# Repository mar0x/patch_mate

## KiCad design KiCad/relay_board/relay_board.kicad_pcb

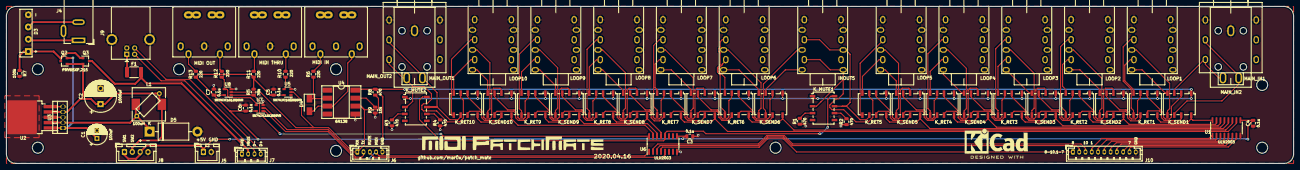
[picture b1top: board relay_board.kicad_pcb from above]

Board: 2 copper layers, 410.0 x 50.0 mm, 83 parts (0 on the bottom side), 136 nets.

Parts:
C1: 100uF; CP_Radial_D6.3mm_P2.50mm
C2: 1000uF; CP_Radial_D10.0mm_P5.00mm
C3, C4, C5, C6, C7: 0.1u; C_0805_2012Metric
D3: RS202-BP; Diode_Bridge_KBP20x
D4: D; D_SMA
D5: 1N5822; D_DO-201AD_P15.24mm_Horizontal
F1: MF-MSMF050-2; Fuse_1812_4532Metric_Pad1.30x3.40mm_HandSolder
INOUT5: AudioJack3_Dual_Switch; CK635-037
J1, J2, J3: DIN5MIDI-OOTDTY
J4: DS-210; BarrelJack_Wuerth_6941xx301002
J5: JST B2B-XH-A; JST_XH_B2B-XH-A_1x02_P2.50mm_Vertical
J6: JST B5B-PH-K-S; JST_PH_B5B-PH-K_1x05_P2.00mm_Vertical
J7: JST B4B-PH-K-S; JST_PH_B4B-PH-K_1x04_P2.00mm_Vertical
J8: JST B4B-XH-A; JST_XH_B4B-XH-A_1x04_P2.50mm_Vertical
J9: DS1099; USB_B_OST_USB-B1HSxx_Horizontal
J10: JST B11B-PH-K-S; JST_PH_B11B-PH-K_1x11_P2.00mm_Vertical
K_MUTE1, K_MUTE2: G6K-2; Relay_DPDT_Omron_G6K-2F-Y
K_RET1, K_RET2, K_RET3, K_RET4, K_RET5, K_RET6, K_RET7, K_RET8, K_RET9, K_RET10: G6K-2; Relay_DPDT_Omron_G6K-2F-Y
K_SEND1, K_SEND2, K_SEND3, K_SEND4, K_SEND5, K_SEND6, K_SEND7, K_SEND8, K_SEND9, K_SEND10: G6K-2; Relay_DPDT_Omron_G6K-2F-Y
L1: 100uH; L_10.4x10.4_H4.8
L2: 100uH; L_Axial_L7.0mm_D3.3mm_P10.16mm_Horizontal_Fastron_MICC
LOOP1, LOOP2, LOOP3, LOOP4, LOOP5, LOOP6, LOOP7, LOOP8, LOOP9, LOOP10: AudioJack3_Dual_Switch; CK635-037
MAIN_IN1: CK635-041A
MAIN_IN2: HLJ0544*; phone-jack-6.3
MAIN_OUT1: CK635-041A
MAIN_OUT2: HLJ0544*; phone-jack-6.3
Q2, Q3: PMV65XP,215; SOT-23
R1, R2, R3, R4, R8: 470; R_0805_2012Metric
R5: 39k; R_0805_2012Metric
R6, R10, R11, R12, R13: 220; R_0805_2012Metric
R7: 100k; R_0805_2012Metric
R9: 10k; R_0805_2012Metric
U1, U6: ULN2003; SOIC-16_3.9x9.9mm_P1.27mm
U2: LM2576S-5.0; TO-263-5_TabPin3
U3: LM2576HVT-5.0; TO-220-5_Vertical
U4: 6N138; DIP-8_W8.89mm_SMDSocket_LongPads
U5, U7, U8: SN74LVC1G125DBVR; SOT-23-5

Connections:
+5V: C3.2, C4.2, C5.2, C6.2, C7.2, J5.1, J8.1, J8.3, K_MUTE1.1, K_MUTE2.1, K_RET1.1, K_RET2.1, K_RET3.1, K_RET4.1, K_RET5.1, K_RET6.1, K_RET7.1, K_RET8.1, K_RET9.1, K_RET10.1, K_SEND1.1, K_SEND2.1, K_SEND3.1, K_SEND4.1, K_SEND5.1, K_SEND6.1, K_SEND7.1, K_SEND8.1, K_SEND9.1, K_SEND10.1, R5.2, R8.2, R11.1, R13.1, U1.9, U4.8, U5.5, U6.9, U7.5, U8.5
+9V: D3.1, Q2.3, Q3.1, R7.1
D+: J7.4, J9.3
D-: J7.3, J9.2
GND: C1.2, C2.2, C3.1, C4.1, C5.1, C6.1, C7.1, D3.4, D5.2, INOUT5.S1, INOUT5.S2, INOUT5.SN1, INOUT5.SN2, J2.2, J3.2, J5.2, J6.5, J7.1, J8.4, J9.4, J9.5, J10.11, LOOP1.S1, LOOP1.S2, LOOP1.SN1, LOOP1.SN2, LOOP2.S1, LOOP2.S2, LOOP2.SN1, LOOP2.SN2, LOOP3.S1, LOOP3.S2, LOOP3.SN1, LOOP3.SN2, LOOP4.S1, LOOP4.S2, LOOP4.SN1, LOOP4.SN2, LOOP5.S1, LOOP5.S2, LOOP5.SN1, LOOP5.SN2, LOOP6.S1, LOOP6.S2, LOOP6.SN1, LOOP6.SN2, LOOP7.S1, LOOP7.S2, LOOP7.SN1, LOOP7.SN2, LOOP8.S1, LOOP8.S2, LOOP8.SN1, LOOP8.SN2, LOOP9.S1, LOOP9.S2, LOOP9.SN1, LOOP9.SN2, LOOP10.S1, LOOP10.S2, LOOP10.SN1, LOOP10.SN2, MAIN_IN1.S, MAIN_IN1.SN, MAIN_IN2.S, MAIN_OUT1.S, MAIN_OUT1.SN, MAIN_OUT2.S, R1.1, R2.1, R3.1, R4.1, R7.2, R9.1, U1.8, U2.3, U2.5, U3.3, U3.5, U4.5, U5.1, U5.3, U6.8, U7.3, U8.3
LOOP1: J10.4, U1.1
LOOP1_R: K_SEND1.6, MAIN_IN1.R, MAIN_IN2.R
LOOP1_T: K_SEND1.3, MAIN_IN1.T, MAIN_IN2.T
LOOP2: J10.5, U1.2
LOOP3: J10.6, U1.3
LOOP4: J10.7, U1.4
LOOP5: J10.8, U1.5
LOOP5_R: INOUT5.R1, INOUT5.RN2, K_MUTE1.7, K_RET5.6
LOOP5_T: INOUT5.T1, INOUT5.TN2, K_MUTE1.2, K_RET5.3
LOOP6: J10.9, U1.6
LOOP6_R: INOUT5.R2, K_SEND6.6
LOOP6_T: INOUT5.T2, K_SEND6.3
LOOP7: J10.10, U1.7
LOOP8: J10.1, U6.4
LOOP9: J10.2, U6.3
LOOP10: J10.3, U6.2
LOOP10_R: K_MUTE2.7, K_RET10.6, MAIN_OUT1.R, MAIN_OUT2.R
LOOP10_T: K_MUTE2.2, K_RET10.3, MAIN_OUT1.T, MAIN_OUT2.T
MIDI_MODE: J6.4, U6.1, U7.1
MIDI_OUT: R12.2, U7.4, U8.4
MUTE: J6.3, U6.5
unnamed: D3.2, J4.1
unnamed: D3.3, J4.2
unnamed: D4.1, R6.1, U4.2
unnamed: D4.2, J1.5, U4.3
unnamed: F1.1, J9.1
unnamed: J1.4, R6.2
unnamed: J2.4, R11.2
unnamed: J2.5, R10.1
unnamed: J3.4, R13.2
unnamed: J3.5, R12.1
unnamed: K_MUTE1.3, R1.2
unnamed: K_MUTE1.6, R2.2
unnamed: K_MUTE2.3, R3.2
unnamed: K_MUTE2.6, R4.2
unnamed: K_RET1.2, K_SEND1.2
unnamed: K_RET1.3, K_SEND2.3
unnamed: K_RET1.4, LOOP1.T1
unnamed: K_RET1.5, LOOP1.R1
unnamed: K_RET1.6, K_SEND2.6
unnamed: K_RET1.7, K_SEND1.7
unnamed: K_RET2.2, K_SEND2.2
unnamed: K_RET2.3, K_SEND3.3
unnamed: K_RET2.4, LOOP2.T1
unnamed: K_RET2.5, LOOP2.R1
unnamed: K_RET2.6, K_SEND3.6
unnamed: K_RET2.7, K_SEND2.7
unnamed: K_RET3.2, K_SEND3.2
unnamed: K_RET3.3, K_SEND4.3
unnamed: K_RET3.4, LOOP3.T1
unnamed: K_RET3.5, LOOP3.R1
unnamed: K_RET3.6, K_SEND4.6
unnamed: K_RET3.7, K_SEND3.7
unnamed: K_RET4.2, K_SEND4.2
unnamed: K_RET4.3, K_SEND5.3
unnamed: K_RET4.4, LOOP4.T1
unnamed: K_RET4.5, LOOP4.R1
unnamed: K_RET4.6, K_SEND5.6
unnamed: K_RET4.7, K_SEND4.7
unnamed: K_RET5.2, K_SEND5.2
unnamed: K_RET5.4, LOOP5.T1
unnamed: K_RET5.5, LOOP5.R1
unnamed: K_RET5.7, K_SEND5.7
unnamed: K_RET6.2, K_SEND6.2
unnamed: K_RET6.3, K_SEND7.3
unnamed: K_RET6.4, LOOP6.T1
unnamed: K_RET6.5, LOOP6.R1
unnamed: K_RET6.6, K_SEND7.6
unnamed: K_RET6.7, K_SEND6.7
unnamed: K_RET7.2, K_SEND7.2
unnamed: K_RET7.3, K_SEND8.3
unnamed: K_RET7.4, LOOP7.T1
unnamed: K_RET7.5, LOOP7.R1
unnamed: K_RET7.6, K_SEND8.6
unnamed: K_RET7.7, K_SEND7.7
unnamed: K_RET8.2, K_SEND8.2
unnamed: K_RET8.3, K_SEND9.3
unnamed: K_RET8.4, LOOP8.T1
unnamed: K_RET8.5, LOOP8.R1
unnamed: K_RET8.6, K_SEND9.6
unnamed: K_RET8.7, K_SEND8.7
unnamed: K_RET9.2, K_SEND9.2
unnamed: K_RET9.3, K_SEND10.3
unnamed: K_RET9.4, LOOP9.T1
unnamed: K_RET9.5, LOOP9.R1
unnamed: K_RET9.6, K_SEND10.6
unnamed: K_RET9.7, K_SEND9.7
unnamed: K_RET10.2, K_SEND10.2
unnamed: K_RET10.4, LOOP10.T1
unnamed: K_RET10.5, LOOP10.R1
unnamed: K_RET10.7, K_SEND10.7
unnamed: K_SEND1.4, LOOP1.T2
unnamed: K_SEND1.5, LOOP1.R2
unnamed: K_SEND2.4, LOOP2.T2
unnamed: K_SEND2.5, LOOP2.R2
unnamed: K_SEND3.4, LOOP3.T2
unnamed: K_SEND3.5, LOOP3.R2
unnamed: K_SEND4.4, LOOP4.T2
unnamed: K_SEND4.5, LOOP4.R2
unnamed: K_SEND5.4, LOOP5.T2
unnamed: K_SEND5.5, LOOP5.R2
unnamed: K_SEND6.4, LOOP6.T2
unnamed: K_SEND6.5, LOOP6.R2
unnamed: K_SEND7.4, LOOP7.T2
unnamed: K_SEND7.5, LOOP7.R2
unnamed: K_SEND8.4, LOOP8.T2
unnamed: K_SEND8.5, LOOP8.R2
unnamed: K_SEND9.4, LOOP9.T2
unnamed: K_SEND9.5, LOOP9.R2
unnamed: K_SEND10.4, LOOP10.T2
unnamed: K_SEND10.5, LOOP10.R2
unnamed: R9.2, U4.7
unnamed: R10.2, U5.4
PWR: C2.1, J8.2, L1.2, L2.2, Q2.1, Q3.2, U2.4, U3.4
REL1: K_RET1.8, K_SEND1.8, U1.16
REL2: K_RET2.8, K_SEND2.8, U1.15
REL3: K_RET3.8, K_SEND3.8, U1.14
REL4: K_RET4.8, K_SEND4.8, U1.13
REL5: K_RET5.8, K_SEND5.8, U1.12
REL6: K_RET6.8, K_SEND6.8, U1.11
REL7: K_RET7.8, K_SEND7.8, U1.10
REL8: K_RET8.8, K_SEND8.8, U6.13
REL9: K_RET9.8, K_SEND9.8, U6.14
REL10: K_RET10.8, K_SEND10.8, U6.15
REL_MUTE: K_MUTE1.8, K_MUTE2.8, U6.12
RX: J6.1, R8.1, U4.6, U5.2, U8.2
TX: J6.2, U7.2
VBUS: F1.2, J7.2, Q3.3
VR_IN: C1.1, Q2.2, U2.1, U3.1
VR_OUT: D5.1, L1.1, L2.1, U2.2, U3.2
~MIDI_MODE: R5.1, U6.16, U8.1

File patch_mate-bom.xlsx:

id | q | ref | desc | size | Vendor |  | Order info
 |  |  |  |  | URL | code | # | date | price | count | shipping | cost | cost per item
Control board
22 pF | 2 | C1,C2 | Кер.ЧИП конд. 22пФ NPO 50В, 5% | 0805 | MLCC22pFNPO50V5%0805 | #29844 |  |  | 4 | 1 |  | 4 | 8
0.1 uF | 9 | C3,C5,C6,C7,C8,C9,C10,C11,C12 | Кер.ЧИП конд. 0.1 мкФ X7R 50В, 10% | 0805 | GRM21BR71H104K | #860640216 |  |  | 7 | 1 |  | 7 | 63
 |  |  |  |  |  | #684373 |  |  | 1.2 | 1 |  | 1.2 | 0
1 uF | 1 | C4 | Кер.ЧИП конд. 1 мкФ X7R 16В, 10% | 0805 | GRM21BR71C105KA01K | #443350645 |  |  | 6 | 1 |  | 6 | 6
JST B2B-XH-A | 1 | J1 | 2.5mm |  | JST XH 2.5 mm 2 pin |  |  |  | 1.45 | 100 | 75 | 220 | 2.2000000000000002
JST B11B-PH-K-S | 1 | J2 | 2.0mm |  | JST 2.0 mm 11 pin |  | #5003346814132510 | 43901 | 10.3065 | 20 |  | 206.13 | 10.3065
JST B4B-PH-K-S | 1 | J3 | 2.0mm |  | JST 2.0 mm 4 pin |  | #5003346814132510 | 43901 | 5.8549999999999995 | 20 |  | 117.1 | 5.8549999999999995
JST B5B-PH-K-S | 1 | J4 | 2.0mm |  | JST 2.0 mm 5 pin |  | #5003346814132510 | 43901 | 6.4965000000000002 | 20 |  | 129.93 | 6.4965000000000002
DS1013-06S | 1 | J5 | Вилка на плату прямая 6 конт. 2.54мм |  | DS1013-06SSiB1-B-0 | #9000058155 |  |  | 7 | 1 |  | 7 | 7
JST B6B-PH-K-S | 1 | J6 | 2.0mm |  | JST 2.0 mm 6 pin |  | #5003346814132510 | 43901 | 7.1784999999999997 | 20 |  | 143.57 | 7.1784999999999997
JST B7B-PH-K-S | 1 | J7 | 2.0mm |  | JST 2.0 mm 7 pin |  | #5003346814132510 | 43901 | 7.94 | 20 |  | 158.80000000000001 | 7.94
1 kOhm | 13 |  | Чип резистор (SMD), 1 кОм, 0.125Вт, 1% | 0805 | RC0805FR-071KL | #9000079486 |  |  | 2 | 1 |  | 2 | 26
22 Ohm | 2 | R12,R13 | Чип резистор (SMD), 22 Ом, 0.125Вт, 1% | 0805 | RC0805FR-0722RL | #9000079446 |  |  | 2 | 1 |  | 2 | 4
10 kOhm | 2 | R14,R15 | Чип резистор (SMD), 10 кОм, 0.125Вт, 1% | 0805 | RC0805FR-0710KL | #9000079514 |  |  | 2 | 1 |  | 2 | 4
39 kOhm | 15 |  | Чип резистор (SMD), 39 кОм, 0.125Вт, 1% | 0805 | RC0805FR-0739KL | #9000079528 |  |  | 2 | 1 |  | 2 | 30
PEC16-2215F-N0024 | 1 |  | Энкодер инкрементный |  | PEC16-2215F-N0024 | #831232642 |  |  | 190 | 1 |  | 190 | 190
 | 0 |  |  |  |  | #577148 |  |  | 44.8 | 1 |  | 44.8 | 0
ATmega32U4-AU | 1 | U1 | Микроконтроллер 8-Бит, AVR, 16МГц, 32КБ Flash, с USB контроллером | TQFP-44 | ATmega32U4 |  | #3003806113682510 |  | 228.8 | 5 |  | 1144 | 228.8
74HC595 | 3 | U2,U6,U7 | 8-и битный сдвиговый регистр с выходным регистром-защелки и тремя состояниями | SO-16 | 74HC595D | #563425591 |  |  | 13 | 1 |  | 13 | 39
USBLC6-2SC6 | 1 | U3 | Защита интерфейса USB от электростатических разрядов | SOT-23-6 | USBLC6-2SC6 | #9000039051 |  |  | 10 | 1 |  | 10 | 10
74HC165 | 2 | U4,U5 | 8-битный сдвиговый регистр с параллельным входом, последовательным выходом | SO-16 | 74HC165D,653 | #56682 |  |  | 12 | 1 |  | 12 | 24
AT25640B | 1 | U8 | Микросхема памяти, 64Kb SPI-compatible Serial EEPROM | SO-8 | AT25640B-SSHL-T | #9000142234 |  |  | 34 | 1 |  | 34 | 34
SN74LVC1G125DBVR | 1 | U9 | Один буферный элемент с тремя состояниями на выходе | SOT-23-5 | SN74LVC1G125DBVR | #9010000228 |  |  | 8 | 1 |  | 8 | 8
HC-49SM | 1 | Y1 | Кварцевый резонатор, 16.000 МГц | HC-49SM | HC-49SM | #375027481 |  |  | 18 | 1 |  | 18 | 18
Relay board
100 uF | 1 | C1 | Конденсатор электролитический алюминиевый, ECAP (К50-35), 100 мкФ, 25 В, 20% | 6.3x11mm | JRC1E101M02500630110000B | #9000565756 |  |  | 5 | 1 |  | 5 | 5
1000 uF | 1 | C2 | Конденсатор электролитический алюминиевый, ECAP (К50-35), 1000 мкФ, 16 В | 10x16mm | B41851A4108M000 | #9000306686 |  |  | 32 | 1 |  | 32 | 32
0.1 uF | 5 | C3,C4,C5,C6,C7 | Кер.ЧИП конд. 0.1 мкФ X7R 50В, 10% | 0805 | GRM21BR71H104K | #860640216 |  |  | 7 | 1 |  | 7 | 35
 |  |  |  |  |  | #684373 |  |  | 1.2 | 1 |  | 1.2 | 0
RS202-BP | 1 | D3 | Diode bridge, +ve/AC/AC/-ve | RS2 | RS202-BP | #8001784108 |  |  | 11 | 1 |  | 11 | 11
D | 1 | D4 | Диод импульсный 75 мА 75В 5нс |  |  |  |  |  |  | 1 |  | 0 | 0
 |  |  |  | SOD323F/SC-90 | BAS316.115 | #241389 |  |  | 0.65 | 1
1N5822 | 1 | D5 | Диод Шоттки 40В 3А/80А | DO-201AE | 1N5822 | #9000087681 |  |  | 12 | 1 |  | 12 | 12
MF-MSMF050-2 | 1 | F1 | Предохранитель USB VBUS | 1812 | MF-MSMF050-2 |  |  |  | 90 | 1 |  | 90 | 90
 |  |  |  |  |  | #186713 |  |  | 2.1 | 1 |  | 2.1 | 0
DualJack | 11 |  |  |  | CK635-037 |  | #3003695040752510 |  | 115 | 10 |  | 1150 | 1265
RTW909080M | 3 | J1,J2,J3 | DIN connector 5 Pin DIN Female Jack Right Angle Panel Mount 90 Degree |  | RTW909080M |  | #5005159492622510 | 44070 | 23.052 | 60 | 141.74 | 1524.86 | 76.242999999999995
DS-210 | 1 | J4 | Гнездо питания 2,1х5,5мм на панель |  | DS-210 |  | #5005159492062510 | 44070 | 3.5819999999999999 | 10 | 65.42 | 101.24000000000001 | 10.124000000000001
JST B2B-XH-A | 1 | J5 | 2.5mm |  | JST XH 2.5 mm 2 pin |  |  |  | 1.45 | 100 |  | 145 | 1.45
JST B5B-PH-K-S | 1 | J6 | 2.0mm |  | JST 2.0 mm 5 pin |  | #5003346814132510 | 43901 | 6.4965000000000002 | 20 |  | 129.93 | 6.4965000000000002
JST B4B-PH-K-S | 1 | J7 | 2.0mm |  | JST 2.0 mm 4 pin |  | #5003346814132510 | 43901 | 5.8549999999999995 | 20 |  | 117.1 | 5.8549999999999995
JST B4B-XH-A | 1 | J8 | 2.5mm |  | JST XH 2.5 mm 4 pin |  |  |  | 2.0714285714285716 | 70 |  | 145 | 2.0714285714285716
DS1099 | 1 | J9 | Розетка на плату, тип B (черная) угловая |  | DS1099-BN0 | #846814658 |  |  | 21 | 1 |  | 21 | 21
 |  |  |  |  | USBB-1J | #1209523 |  |  | 6.1 | 1 |  | 6.1 | 0
JST B11B-PH-K-S | 1 | J10 | 2.0mm |  | JST 2.0 mm 11 pin |  | #5003346814132510 | 43901 | 10.3065 | 20 |  | 206.13 | 10.3065
G6K-2F-Y | 22 |  | Relay |  | G6K2FYTR5DC |  | #06867934 |  | 129 | 20 |  | 2580 | 2838
100 uH | 1 | L1 | Катушка индуктивности, КИ (КИГ) 3.0-100 мкГн, 10%-20% |  | КИГ3.0-100мкГн | #44315 |  |  | 120 | 1 |  | 120 | 120
 |  |  |  |  |  | #36959 |  |  | 88 | 1 |  | 88 | 0
CK635-041A | 2 |  | Audio Jack, 3 Poles (Stereo / TRS) |  | AudioJack Socket |  | #8003284014042510 | 43738 | 40 | 5 |  | 200 | 80
PMV65XP,215 | 2 | Q2,Q3 | Транзистор MOSFET P-CH 20V 3.9A 76 mOhm | SOT-23-3 | PMV65XP,215 |  |  |  | 8 | 1 |  | 8 | 16
470 Ohm | 5 | R1,R2,R3,R4,R8 | Чип резистор (SMD), 470 Ом, 0.125Вт, 1%, 0805 | 0805 | RC0805FR-07470RL | #9000079478 |  |  | 2 | 1 |  | 2 | 10
39 kOhm | 1 | R5 | Чип резистор (SMD), 39 кОм, 0.125Вт, 1%, 0805 | 0805 | RC0805FR-0739KL | #9000079528 |  |  | 2 | 1 |  | 2 | 2
220 Ohm | 5 | R6,R10,R11,R12,R13 | Чип резистор (SMD), 220 Ом, 0.125Вт, 1%, 0805 | 0805 | RC0805FR-07220RL | #9000079470 |  |  | 2 | 1 |  | 2 | 10
100 kOhm | 1 | R7 | Чип резистор (SMD), 100 кОм, 0.125Вт, 1%, 0805 | 0805 | RC0805FR-07100KL | #9000079538 |  |  | 2 | 1 |  | 2 | 2
10 kOhm | 1 | R9 | Чип резистор (SMD), 10 кОм, 0.125Вт, 1%, 0805 | 0805 | RC0805FR-0710KL | #9000079514 |  |  | 2 | 1 |  | 2 | 2
ULN2003 | 2 | U1,U6 | Матрица из семи транзисторов Дарлингтона, 500мА | SO-16 | ULN2003ADR |  |  |  | 30 | 1 |  | 30 | 60
LM2576HVT-5.0 | 0 | U3 | Импульсный понижающий регулятор напряжения, 5В, 3А | TO-220-5 | LM2576HVT-5.0 |  |  |  | 370 | 1 |  | 370 | 0
 | 1 |  |  |  |  | #32785463847 | #94453833502510 | 43346 | 12.620000000000001 | 10 | 63.1 | 189.3 | 18.93
6N138M | 1 | U4 | Оптопара с транзисторным выходом | SMD DIP-8 | 6N138M |  | #5005159492502510 | 44070 | 8.8780000000000001 | 10 | 53.74 | 142.52000000000001 | 14.252000000000001
SN74LVC1G125DBVR | 3 | U5,U7,U8 | Один буферный элемент с тремя состояниями на выходе | SOT-23-5 | SN74LVC1G125DBVR | #9010000228 |  |  | 8 | 1 |  | 8 | 24
Other
1602 OLED | 1 |  |  |  | 1602 OLED |  | 5003448406902510 |  | 1050 | 1 | 280 | 1330 | 1330
6x6x7 Tact Button | 13 |  |  |  | 6x6x7 Tact Button |  | 3003743130452510 | 43938 | 75 | 1 |  | 75 | 975
Button Cap | 13 |  |  |  | Button Cap 10 mm |  |  |  | 55 | 1 |  | 55 | 715
PCB | 1 |  |  |  |  |  |  |  | 311 | 5 | 1500 | 3055 | 611
Button Board PCB | 1 |  |  |  |  |  |  |  | 657.6 | 5 |  | 3288 | 657.6
Power Switch | 1 |  |  |  | Latched Button, 16 mm, Green, 5v |  | #93387171242510 | 43312 | 144 | 1 |  | 144 | 144
 |  |  |  |  |  |  |  |  |  |  |  |  | 9953.1049285714289

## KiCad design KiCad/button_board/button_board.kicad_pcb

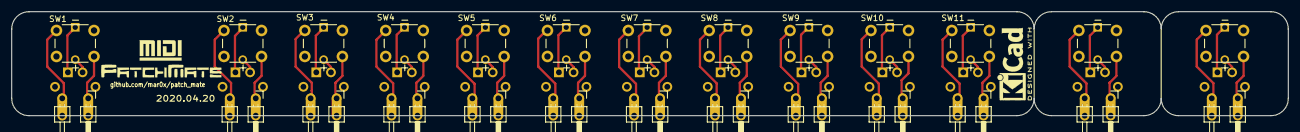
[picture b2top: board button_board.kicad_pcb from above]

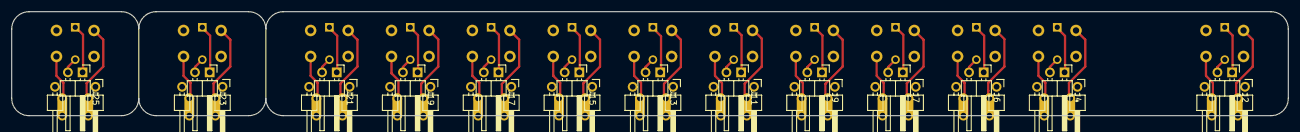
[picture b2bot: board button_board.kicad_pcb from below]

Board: 2 copper layers, 221.0 x 18.0 mm, 39 parts (13 on the bottom side), 52 nets.

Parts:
J1, J3, J5, J8, J10, J12, J14, J16, J18, J20, J22, J24, J26: Conn_01x02_Male; PinHeader_1x02_P4.5mm_Horizontal
J2, J4, J6, J7, J9, J11, J13, J15, J17, J19, J21, J23, J25: Conn_01x02_Male; PinHeader_1x02_P2.54mm_Horizontal
SW1, SW2, SW3, SW4, SW5, SW6, SW7, SW8, SW9, SW10, SW11, SW12, SW13: SW_MEC_5G_LED; SW_PUSH_6mm

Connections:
unnamed: J1.1, SW1.4
unnamed: J1.2, SW1.1
unnamed: J2.1, SW1.2
unnamed: J2.2, SW1.3
unnamed: J3.1, SW2.4
unnamed: J3.2, SW2.1
unnamed: J4.1, SW2.2
unnamed: J4.2, SW2.3
unnamed: J5.1, SW3.4
unnamed: J5.2, SW3.1
unnamed: J6.1, SW3.2
unnamed: J6.2, SW3.3
unnamed: J7.1, SW4.2
unnamed: J7.2, SW4.3
unnamed: J8.1, SW4.4
unnamed: J8.2, SW4.1
unnamed: J9.1, SW5.2
unnamed: J9.2, SW5.3
unnamed: J10.1, SW5.4
unnamed: J10.2, SW5.1
unnamed: J11.1, SW6.2
unnamed: J11.2, SW6.3
unnamed: J12.1, SW6.4
unnamed: J12.2, SW6.1
unnamed: J13.1, SW7.2
unnamed: J13.2, SW7.3
unnamed: J14.1, SW7.4
unnamed: J14.2, SW7.1
unnamed: J15.1, SW8.2
unnamed: J15.2, SW8.3
unnamed: J16.1, SW8.4
unnamed: J16.2, SW8.1
unnamed: J17.1, SW9.2
unnamed: J17.2, SW9.3
unnamed: J18.1, SW9.4
unnamed: J18.2, SW9.1
unnamed: J19.1, SW10.2
unnamed: J19.2, SW10.3
unnamed: J20.1, SW10.4
unnamed: J20.2, SW10.1
unnamed: J21.1, SW11.2
unnamed: J21.2, SW11.3
unnamed: J22.1, SW11.4
unnamed: J22.2, SW11.1
unnamed: J23.1, SW12.2
unnamed: J23.2, SW12.3
unnamed: J24.1, SW12.4
unnamed: J24.2, SW12.1
unnamed: J25.1, SW13.2
unnamed: J25.2, SW13.3
unnamed: J26.1, SW13.4
unnamed: J26.2, SW13.1

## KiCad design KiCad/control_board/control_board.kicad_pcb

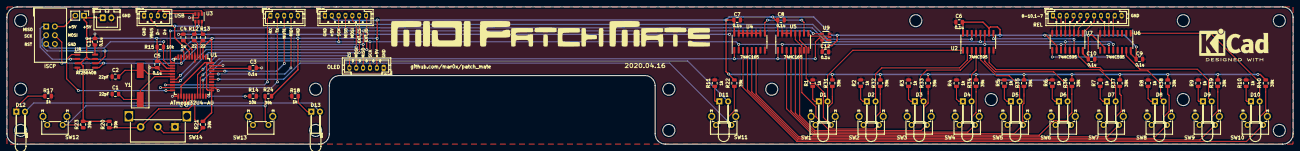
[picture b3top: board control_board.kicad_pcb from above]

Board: 2 copper layers, 375.0 x 40.0 mm, 89 parts (0 on the bottom side), 83 nets.

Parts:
C1, C2: 22pF; C_0805_2012Metric
C3, C5, C6, C7, C8, C9, C10, C11, C12: 0.1u; C_0805_2012Metric
C4: 1u; C_0805_2012Metric
D1, D2, D3, D4, D5, D6, D7, D8, D9, D10, D11, D12, D13: LED; LED_D3.0mm_Horizontal_O6.35mm_Z10.0mm
J1: JST B2B-XH-A; JST_XH_B2B-XH-A_1x02_P2.50mm_Vertical
J2: JST B11B-PH-K-S; JST_PH_B11B-PH-K_1x11_P2.00mm_Vertical
J3: JST B4B-PH-K-S; JST_PH_B4B-PH-K_1x04_P2.00mm_Vertical
J4: JST B5B-PH-K-S; JST_PH_B5B-PH-K_1x05_P2.00mm_Vertical
J5: DS1013-06S; IDC-Header_2x03_P2.54mm_Vertical
J6: JST B6B-PH-K-S; JST_PH_B6B-PH-K_1x06_P2.00mm_Vertical
J7: JST B7B-PH-K-S; JST_PH_B7B-PH-K_1x07_P2.00mm_Vertical
J8: Conn_01x02_Male; PinHeader_1x02_P2.54mm_Vertical
R1, R2, R3, R4, R5, R6, R7, R8, R9, R10, R11, R17, R18: 1k; R_0805_2012Metric
R12, R13: 22; R_0805_2012Metric
R14, R15: 10k; R_0805_2012Metric
R20, R21, R22, R23, R24, R31, R32, R33, R34, R35, R36, R37, R38, R39, R40: 39k; R_0805_2012Metric
SW1, SW2, SW3, SW4, SW5, SW6, SW7, SW8, SW9, SW10, SW11, SW12, SW13: SW_Push; SW_Tactile_SPST_Angled_PTS645Vx83-2LFS
SW14: PEC16-2215F-N0024; RotaryEncoder_Bourns_PEC16-2215F-N0024_Vertical
U1: ATmega32U4-AU; TQFP-44_10x10mm_P0.8mm
U2, U6, U7: 74HC595; SOIC-16_3.9x9.9mm_P1.27mm
U3: USBLC6-2SC6; SOT-23-6
U4, U5: 74HC165; SOIC-16_3.9x9.9mm_P1.27mm
U8: AT25640B; SO-8_3.9x4.9mm_P1.27mm
U9: SN74LVC1G125DBVR; SOT-23-5
Y1: HC-49SM; Crystal_SMD_HC49-SD

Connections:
+5V: C5.1, C6.1, C7.1, C8.1, C9.1, C10.1, C11.1, C12.1, J1.1, J6.2, J7.2, J8.1, R15.1, R20.1, R21.1, R22.1, R23.1, R24.1, R31.1, R32.1, R33.1, R34.1, R35.1, R36.1, R37.1, R38.1, R39.1, R40.1, U1.2, U1.14, U1.24, U1.34, U1.44, U2.10, U2.16, U4.16, U5.16, U6.10, U6.16, U7.10, U7.16, U8.3, U8.7, U8.8, U9.5
D1: D1.2, U2.1
D2: D2.2, U2.2
D3: D3.2, U2.3
D4: D4.2, U2.4
D5: D5.2, U2.5
D6: D6.2, U2.6
D7: D7.2, U2.7
D8: D8.2, U7.15
D9: D9.2, U6.15
D10: D10.2, U6.1
D+: R12.1, U1.4
D-: R13.1, U1.3
D_MIDI: D12.2, D13.2, U1.27
D_STORE: D11.2, U1.32
EEPROM_CS: U1.22, U8.1
EXT_CS: J7.6, U1.19
EXT_IO: J7.7, U1.18
GND: C1.2, C2.2, C3.1, C4.1, C5.2, C6.2, C7.2, C8.2, C9.2, C10.2, C11.2, C12.2, J1.2, J2.11, J3.1, J4.5, J5.6, J6.1, J7.1, R1.1, R2.1, R3.1, R4.1, R5.1, R6.1, R7.1, R8.1, R9.1, R10.1, R11.1, R14.1, R17.1, R18.1, SW1.2, SW2.2, SW3.2, SW4.2, SW5.2, SW6.2, SW7.2, SW8.2, SW9.2, SW10.2, SW11.2, SW12.2, SW13.2, SW14.C, U1.5, U1.15, U1.23, U1.35, U1.43, U2.8, U2.13, U3.2, U4.8, U4.10, U4.11, U4.12, U4.13, U4.14, U4.15, U5.8, U5.13, U5.14, U5.15, U6.8, U6.13, U7.8, U7.13, U8.4, U9.3
ISCP_5V: J5.2, J8.2
LOOP1: J2.4, U7.4
LOOP2: J2.5, U7.3
LOOP3: J2.6, U7.2
LOOP4: J2.7, U7.1
LOOP5: J2.8, U6.7
LOOP6: J2.9, U6.6
LOOP7: J2.10, U6.5
LOOP8: J2.1, U7.7
LOOP9: J2.2, U7.6
LOOP10: J2.3, U7.5
MIDI_MODE: J4.4, U1.40
MISO: J5.1, J6.4, J7.4, U1.11, U8.2, U9.4
MOSI: J5.4, J6.5, J7.5, U1.10, U2.14, U8.5
MUTE: J4.3, U1.41
unnamed: C1.1, U1.17, Y1.1
unnamed: C2.1, U1.16, Y1.2
unnamed: C3.2, U1.42
unnamed: C4.2, U1.6
unnamed: D1.1, R1.2
unnamed: D2.1, R2.2
unnamed: D3.1, R3.2
unnamed: D4.1, R4.2
unnamed: D5.1, R5.2
unnamed: D6.1, R6.2
unnamed: D7.1, R7.2
unnamed: D8.1, R8.2
unnamed: D9.1, R9.2
unnamed: D10.1, R10.2
unnamed: D11.1, R11.2
unnamed: D12.1, R17.2
unnamed: D13.1, R18.2
unnamed: J3.3, U3.1
unnamed: J3.4, U3.3
unnamed: R12.2, U3.4
unnamed: R13.2, U3.6
unnamed: R14.2, U1.33
unnamed: U4.9, U5.10
unnamed: U5.9, U9.2
OLED_CS: J6.6, U1.30
REL_CS: U1.12, U2.12, U6.12, U7.12
RE_A: R20.2, SW14.A, U1.28
RE_B: R21.2, SW14.B, U1.29
RST: J5.5, R15.2, U1.13
RX: J4.1, U1.20
SCK: J5.3, J6.3, J7.3, U1.9, U2.11, U4.2, U5.2, U6.11, U7.11, U8.6
SER2: U2.9, U7.14
SER3: U6.14, U7.9
SW1: R31.2, SW1.1, U5.11
SW2: R32.2, SW2.1, U5.12
SW3: R33.2, SW3.1, U5.6
SW4: R34.2, SW4.1, U5.5
SW5: R35.2, SW5.1, U5.4
SW6: R36.2, SW6.1, U5.3
SW7: R37.2, SW7.1, U4.6
SW8: R38.2, SW8.1, U4.5
SW9: R39.2, SW9.1, U4.4
SW10: R40.2, SW10.1, U4.3
SW_CS: U1.31, U4.1, U5.1, U9.1
SW_LEFT: R23.2, SW12.1, U1.25
SW_RIGHT: R24.2, SW13.1, U1.26
SW_STORE: R22.2, SW11.1, U1.38
TX: J4.2, U1.21
VBUS: J3.2, U1.7, U3.5

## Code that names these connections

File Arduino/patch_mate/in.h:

#pragma once

#include <HardwareSerial.h>

#include "artl/button.h"
#include "artl/encoder.h"

#include "artl/digital_out.h"
#include "artl/digital_in.h"

#include "artl/bit_order.h"
#include "artl/piso.h"
#include "artl/pin_change_int.h"

#include "config.h"

namespace patch_mate {

template<typename T>
struct in {
    using traits = T;

    in();

    void setup();
    void update(unsigned long t, bool slow);

    static constexpr
    HardwareSerial& midi() {
#if defined(HAVE_HWSERIAL1)
        return Serial1;
#else
        return Serial;
#endif
    }

    using button_type = artl::button<typename traits::button_handler>;

    const button_type& loop(uint8_t i) const { return loop_[i]; }
    const button_type& left() const { return left_; }
    const button_type& right() const { return right_; }
    const button_type& store() const { return store_; }

private:
    /* 2x 74HC165 pinout
           +8 
      pin  msb  lsb  desc
      --------------------
       A    0    7   LOOP 1 (0)
       B    1    6   LOOP 2 (1)
       C    2    5   LOOP 3 (2)
       D    3    4   LOOP 4 (3)
       E    4    3   NC -> LOOP 8 (7) !!!
       F    5    2   LOOP 7 (6)
       G    6    1   LOOP 6 (5)
       H    7    0   LOOP 5 (4)
      CLK_INH        NC -> GND        !!!

                 +8
      pin  msb  lsb  desc
      --------------------
       A    0    7   LEFT
       B    1    6   STORE
       C    2    5   NC -> GND        !!!
       D    3    4   RIGHT
       E    4    3   GND
       F    5    2   GND
       G    6    1   GND
       H    7    0   GND

      QH'            A2
      CLK            A1
      SH/LD          A0

     */
    enum lsb_bits {
        LEFT  = 15,
        RIGHT = 12,
        STORE = 14,
        LOOP0 = 7,
        LOOP1 = 6,
        LOOP2 = 5,
        LOOP3 = 4,
        LOOP4 = 0,
        LOOP5 = 1,
        LOOP6 = 2,
        LOOP7 = 3,
    };

    enum {
        enc_a_pin = artl::pin::id::mini_13,  // or micro_15
        enc_b_pin = artl::pin::id::mini_12,  // or micro_14
    };

    using enc_a_in = artl::digital_in< enc_a_pin >;
    using enc_b_in = artl::digital_in< enc_b_pin >;

    using enc_a_int = artl::pin_change_int< enc_a_pin >;
    using enc_b_int = artl::pin_change_int< enc_a_pin >;

    using ld = artl::digital_out<A0>;
    using clk = artl::digital_out<A1>;
    using qh = artl::digital_in<A2>;

    using piso_t = uint16_t;
    using piso = artl::piso<piso_t, artl::lsb_first, qh, ld, clk>;

    using encoder_type = artl::encoder<typename traits::encoder_handler>;

    piso_t val_;

    button_type loop_[8];
    button_type left_;
    button_type right_;
    button_type store_;
    encoder_type encoder_;
};

template<typename T> inline
in<T>::in() :
    loop_{ 0, 1, 2, 3, 4, 5, 6, 7 },
    left_(traits::LEFT),
    right_(traits::RIGHT),
    store_(traits::STORE)
{ }

template<typename T> inline void
in<T>::setup()
{
    enc_a_in().setup();
    enc_b_in().setup();
    piso().setup();

    qh().setup();
    val_ = piso().read();

    midi().begin(31250);

    enc_a_int().enable();
    enc_b_int().enable();
}

template<typename T> inline void
in<T>::update(unsigned long t, bool slow)
{
    encoder_.update(enc_a_in().read(), enc_b_in().read(), t);

    if (!slow) return;

    qh().setup();
    val_ = piso().read();

    static const uint8_t m[] = { LOOP0, LOOP1, LOOP2, LOOP3, LOOP4, LOOP5, LOOP6, LOOP7 };

    for (uint8_t i = 0; i < 8; i++) {
        loop_[i].update((val_ & (1 << m[i])) == 0, t);
    }

    store_.update((val_ & (1 << STORE)) == 0, t);
    left_.update((val_ & (1 << LEFT)) == 0, t);
    right_.update((val_ & (1 << RIGHT)) == 0, t);
}

}

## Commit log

2018-10-17 Fritzing files added
2018-10-19 Added .gitignore
2018-10-19 Output connection info updated
2018-10-19 Added missing PCB connections
2018-10-19 Added _lite suffix for in.h and out.h files
2018-10-19 Lite board added
2018-10-25 MIDI Monitor and MIDI output introduced
2018-10-26 Fixing loop 5-8 bits for full-size board
2018-10-26 Removing outdated encoder connections
2018-10-26 Ignoring tags file
2018-10-26 Debug messages review
2018-10-29 Counting controllers from 0
2019-02-15 One more small internal board for USB (B).
2019-02-15 Updating artl.
2019-02-15 Bulk update.
    - MIDI Forwarding (mirror all incoming commands to out port)
    - MIDI In and Out monitors always enabled
    - Display modes for MIDI monitors
    - PC mock introduced (using (n)curses)
2019-02-15 Changing Human Readable MIDI commands.
    Channels are displayed starting from 1;
    Programs are displayed starting from 1;
    Other values are displayed "as is".
2020-02-28 Adding gerber files for PCBs.
2020-02-28 Fixing dead aliexpress links.
    Adding Arduino Pro Micro link.
2020-02-28 Adding MIDI socket alternative link.
2020-03-08 Updating .gitignore file.
2020-03-08 Adding KiCad projects.
2020-03-17 Adding 2 more channels.
2020-03-17 Adding KBP20x diode bridge.
2020-03-17 Adding PEC16 encoder footprint.
2020-03-25 Logo
2020-04-17 Ready for production 2020.04.16
2020-05-05 Updating ignore patterns
2020-05-05 Add one more dimension
2020-05-05 Adding experimental button board
2020-07-06 Added background logo files
2020-07-06 Added images
2020-07-06 Added firmware
2020-07-06 Removing bin files
2020-10-22 Updating voltage regulator part.
2020-10-22 Actual BOM
2020-12-25 Updating BOM.
2021-01-17 Introducting patchmate board package.
2021-01-17 Updating firmware.
2021-01-17 Introducing docs.
2021-01-17 Changing master mode wording.
2021-01-17 Renaming bootloader files.
2021-01-17 Package 1.0.2 update.
2021-02-01 Introducing startup banner.
2021-03-13 Splitting PatchMate and PatchMateX boards.
2021-03-13 Introducing USB MIDI bridge.
2021-12-10 Various fixes and improvements.
2021-12-10 Updating version.
2021-12-24 Change program with encoder.
2021-12-24 Package 1.0.4 update.
    Updating USB attributes.
2021-12-24 Documentation files added.
2021-12-24 Removing outdated PatchMate8.
2021-12-26 Adding changelog.
2021-12-26 Fixing MIDI command extraction.
    For some SysEx data command() may return non-zero which lead to skip
    MIDI event by USB stack. Affects only MIDI->USB data pass.
2021-12-26 Updating version.
    FW-2021.12.26.
2021-12-28 Introducing MIDI Dump.
2021-12-28 Updating docs.
2022-05-14 Fixing file mode.
